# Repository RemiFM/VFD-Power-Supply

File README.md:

# VFD Power Supply

Power supply for the GP1294AI & GP1278BI (also marketed as VFD25648) vacuum fluorescent display. The supply requires a 12V input source, and outputs the necessary voltages to drive the anodes and filaments of the display. 

> [!CAUTION]
> The power supply outputs **voltages up to 75V** DC which can be hazardous. Handle with care.

## Usage
The VFD Display can be soldered to the front of the PCB. All components of the power supply are surface-mount technology (SMT) and are placed on the backside of the PCB. Only connect the display to the PCB after verifying all voltages on the power supply using the provided measuring points. The display can be controlled using any microcontroller that uses 3V3 logic (ESP32, Raspberry Pi...) using the general purpose 2.54mm male headers on the board.

## Ordering PCB
The production files necessary for manufacturing are bundled in the compressed folders [export/GP1294AI.zip](export/GP1294AI.zip) or [export/GP1278BI.zip](export/GP1278BI.zip), depending on the specific VFD display used. The gerber files are generated according to the guidelines of fabrication house JLCPCB. It is recommended to order the PCB from JLCPCB by uploading the compressed folder to their website, but other manufacturers (PCBWay, Eurocircuits...) should work as well.

## Ordering Components
A bill of materials (BOM) is available for download. The BOM contains Digi-Key part numbers, and is formatted in a way that can be uploaded to the Digi-Key website for effortless ordering.
Alternatively, the URL below leads to a public product list on Digi-Key which can be used for ordering the parts. As of June 2024, the total component cost is ~€23.

> [!TIP]
> Order all necessary components by following [this link](https://www.digikey.be/nl/mylists/list/VK1I6PIG8G). 

## Assembly
For assembly, please make use of the provided [schematic](schematic.pdf), available in pdf format.

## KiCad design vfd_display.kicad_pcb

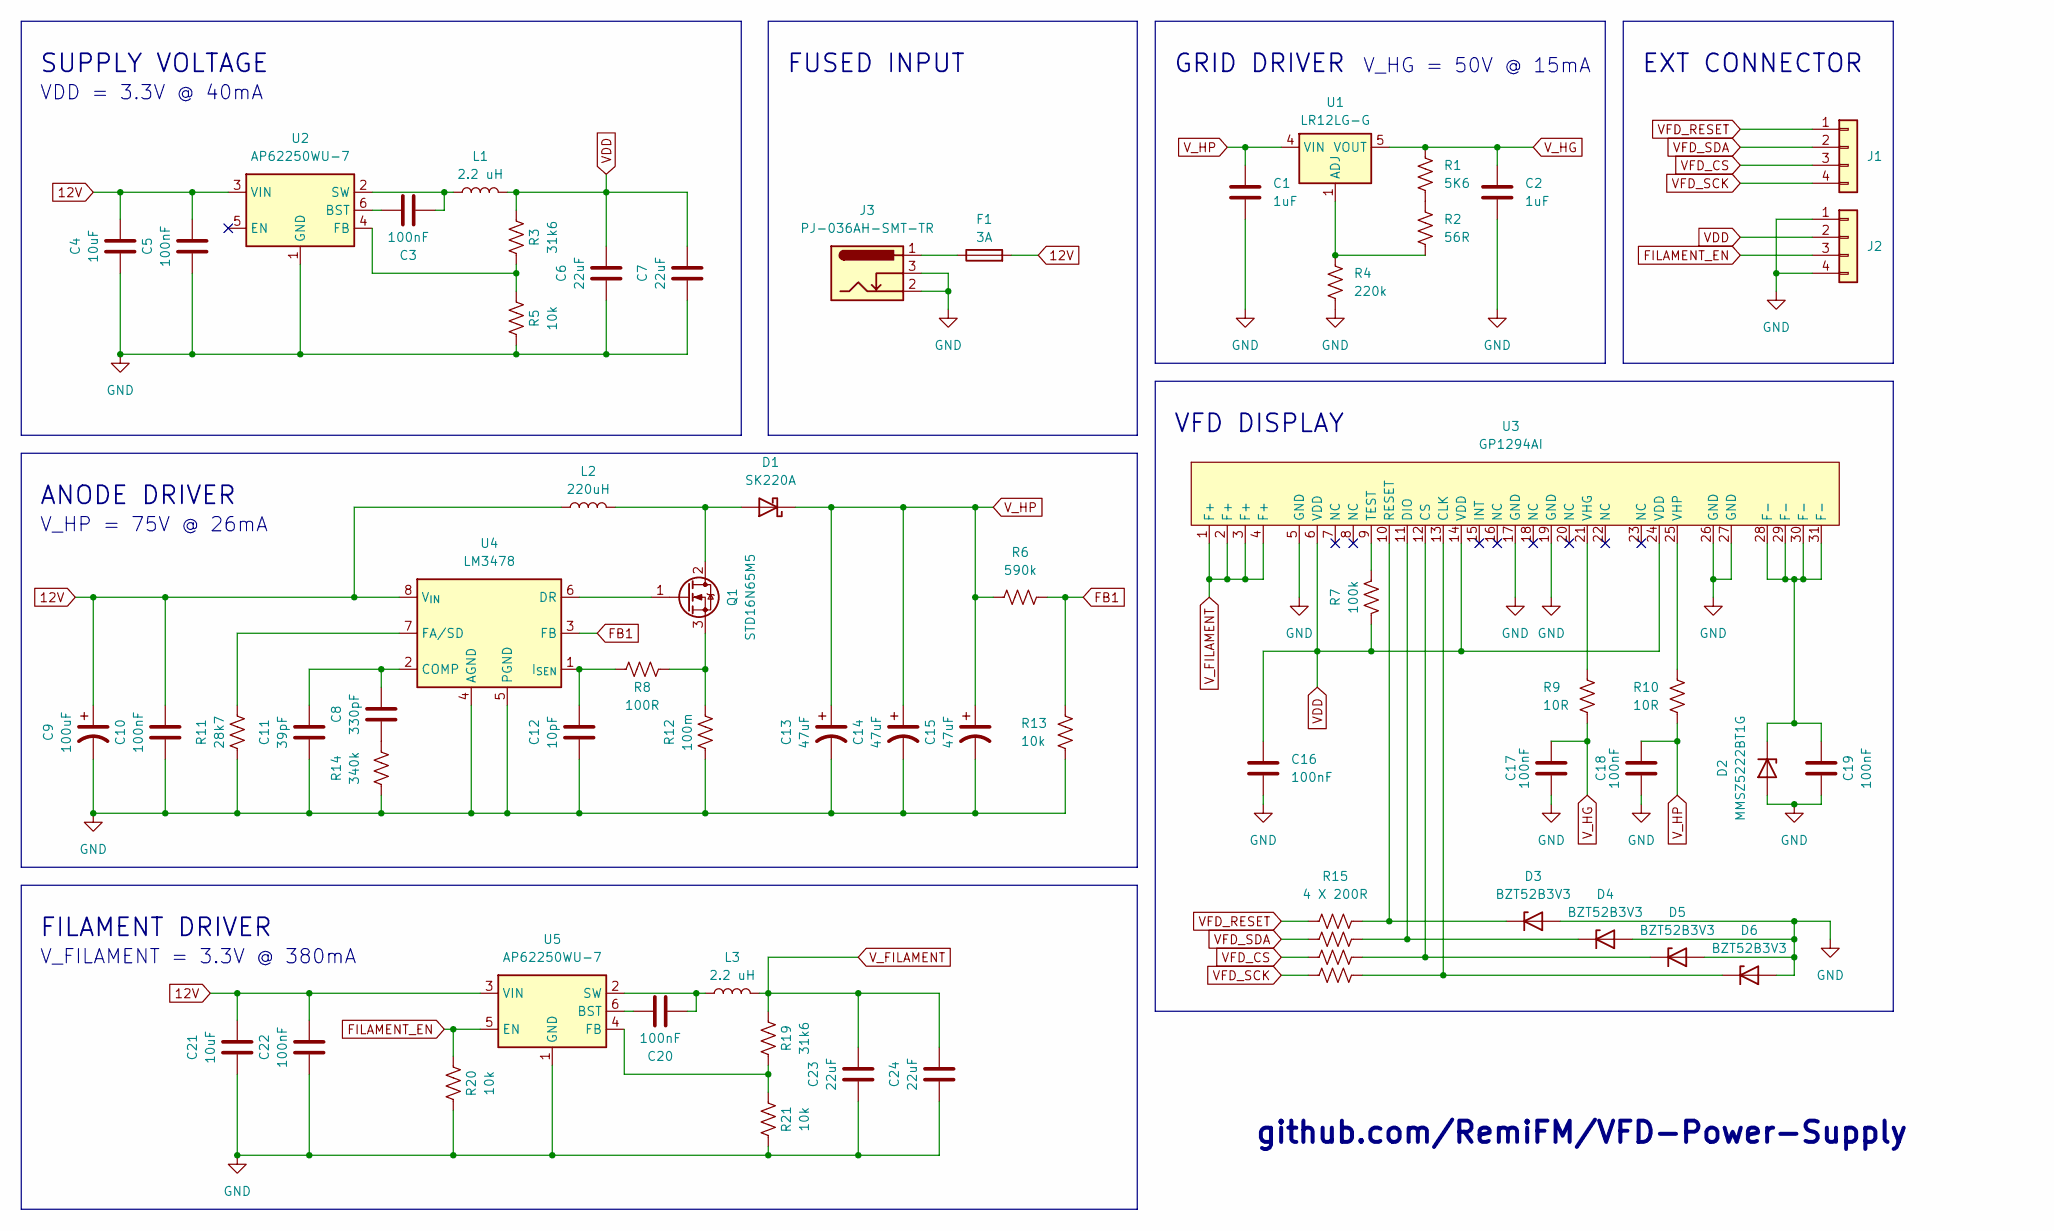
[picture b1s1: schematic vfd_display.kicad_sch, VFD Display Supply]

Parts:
C1, C2: 1uF; C_0805_2012Metric_Pad1.18x1.45mm_HandSolder
C3, C5, C10, C16, C17, C18, C19, C20, C22: 100nF; C_0805_2012Metric_Pad1.18x1.45mm_HandSolder
C4, C21: 10uF; C_0805_2012Metric_Pad1.18x1.45mm_HandSolder
C6, C7, C23, C24: 22uF; C_0805_2012Metric_Pad1.18x1.45mm_HandSolder
C8: 330pF; C_0805_2012Metric_Pad1.18x1.45mm_HandSolder
C9: 100uF; CP_Elec_6.3x7.7; Digi-Key 732-8254-1-ND
C11: 39pF; C_0805_2012Metric_Pad1.18x1.45mm_HandSolder
C12: 10pF; C_0805_2012Metric_Pad1.18x1.45mm_HandSolder
C13, C14, C15: 47uF; CP_Elec_10x10.5; Digi-Key 732-865060857005CT-ND
D1: SK220A; D_SMA_Handsoldering; Digi-Key 1655-SK220ACT-ND
D2: MMSZ5222BT1G; D_SOD-123; Digi-Key MMSZ5222BT1GOSCT-ND
D3, D4, D5, D6: BZT52B3V3; D_SOD-123F
F1: 3A; Fuse_0805_2012Metric_Pad1.15x1.40mm_HandSolder; DigiKeu MFU0805FF03000P100
J1: Conn_01x04; M20-8900405; Digi-Key 952-3265-ND
J2: Conn_01x04; M20-8900405; Digi-Key M20-8900405
J3: PJ-036AH-SMT-TR; BarrelJack_CUI_PJ-036AH-SMT_Horizontal
L1, L3: 2.2 uH; L_1008_2520Metric_Pad1.43x2.20mm_HandSolder; DigiKey 732-9690-1-ND
L2: 220uH; L_Wuerth_WE-PD-Typ-LS_Handsoldering; DigiKey 732-1696-1-ND
Q1: STD16N65M5; Digi-Key 497-8774-1-ND
R1: 5K6; R_0805_2012Metric_Pad1.20x1.40mm_HandSolder
R2: 56R; R_0805_2012Metric_Pad1.20x1.40mm_HandSolder
R3, R19: 31k6; R_0805_2012Metric_Pad1.20x1.40mm_HandSolder
R4: 220k; R_0805_2012Metric_Pad1.20x1.40mm_HandSolder
R5, R13, R20, R21: 10k; R_0805_2012Metric_Pad1.20x1.40mm_HandSolder
R6: 590k; R_0805_2012Metric_Pad1.20x1.40mm_HandSolder
R7: 100k; R_0805_2012Metric_Pad1.20x1.40mm_HandSolder
R8: 100R; R_0805_2012Metric_Pad1.20x1.40mm_HandSolder
R9, R10: 10R; R_0805_2012Metric_Pad1.20x1.40mm_HandSolder
R11: 28k7; R_0805_2012Metric_Pad1.20x1.40mm_HandSolder
R12: 100m; R_0805_2012Metric_Pad1.20x1.40mm_HandSolder
R14: 340k; R_0805_2012Metric_Pad1.20x1.40mm_HandSolder
R15: 4 X 200R; R_0805_2012Metric_Pad1.20x1.40mm_HandSolder
R16, R17, R18: 200R; R_0805_2012Metric_Pad1.20x1.40mm_HandSolder
U1: LR12LG-G; SOIC-8_3.9x4.9mm_P1.27mm; Digi-Key LR12LG-GCT-ND
U2, U5: AP62250WU-7; TSOT26
U3: GP1294AI; VFD_GP1294AI
U4: LM3478; SOIC-8_3.9x4.9mm_P1.27mm; Digi-Key 296-38111-1-ND

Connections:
12V: C4.1, C5.1, C9.1, C10.1, C21.1, C22.1, F1.2, L2.1, U2.3 (VIN), U4.8 (V_{IN}), U5.3 (VIN); also elsewhere on the board
FB1: R6.2, R13.1, U4.3 (FB)
FILAMENT_EN: J2.3, R20.2, U5.5 (EN)
GND: C1.2, C2.2, C4.2, C5.2, C6.2, C7.2, C9.2, C10.2, C11.2, C12.2, C13.2, C14.2, C15.2, C16.1, C17.2, C18.2, C19.2, C21.2, C22.2, C23.2, C24.2, D2.2 (A), D3.2 (A), D4.2 (A), D5.2 (A), D6.2 (A), J2.1, J2.4, J3.2, J3.3, R4.2, R5.1, R11.2, R12.2, R13.2, R14.2, R20.1, R21.1, U2.1 (GND), U3.5 (GND), U3.17 (GND), U3.19 (GND), U3.26 (GND), U3.27 (GND), U4.4 (AGND), U4.5 (PGND), U5.1 (GND); also elsewhere on the board
unnamed: C8.2, R14.1
unnamed: D1.2 (A), L2.2, Q1.2 (D)
unnamed: C19.1, D2.1 (K), U3.28 (F-), U3.29 (F-), U3.30 (F-), U3.31 (F-)
unnamed: D3.1 (K), R15.2, U3.10 (RESET)
unnamed: D4.1 (K), R16.2, U3.11 (DIO)
unnamed: D5.1 (K), R17.2, U3.12 (CS)
unnamed: D6.1 (K), R18.2, U3.13 (CLK)
unnamed: F1.1, J3.1
unnamed: Q1.1 (G), U4.6 (DR)
unnamed: Q1.3 (S), R8.2, R12.1
unnamed: R1.2, R2.1
unnamed: R2.2, R4.1, U1.1 (ADJ)
unnamed: C3.1, U2.6 (BST)
unnamed: R3.1, R5.2, U2.4 (FB)
unnamed: C3.2, L1.1, U2.2 (SW)
unnamed: R7.2, U3.9 (TEST)
unnamed: R9.1, U3.21 (VHG)
unnamed: R10.1, U3.25 (VHP)
unnamed: C8.1, C11.1, U4.2 (COMP)
unnamed: R11.1, U4.7 (FA/SD)
unnamed: C12.1, R8.1, U4.1 (I_{SEN})
unnamed: C20.1, U5.6 (BST)
unnamed: R19.1, R21.2, U5.4 (FB)
unnamed: C20.2, L3.1, U5.2 (SW)
VDD: C6.1, C7.1, C16.2, J2.2, L1.2, R3.2, R7.1, U3.6 (VDD), U3.14 (VDD), U3.24 (VDD); also elsewhere on the board
VFD_CS: J1.3, R17.1
VFD_RESET: J1.1, R15.1
VFD_SCK: J1.4, R18.1
VFD_SDA: J1.2, R16.1
V_FILAMENT: C23.1, C24.1, L3.2, R19.2, U3.1 (F+), U3.2 (F+), U3.3 (F+), U3.4 (F+); also elsewhere on the board
V_HG: C2.1, C17.1, R1.1, R9.2, U1.5 (VOUT); also elsewhere on the board
V_HP: C1.1, C13.1, C14.1, C15.1, C18.1, D1.1 (K), R6.1, R10.2, U1.4 (VIN); also elsewhere on the board

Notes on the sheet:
V_FILAMENT = 3.3V @ 380mA
SUPPLY VOLTAGE
VDD = 3.3V @ 40mA
FUSED INPUT
EXT CONNECTOR
V_HP = 75V @ 26mA
GRID DRIVER
FILAMENT DRIVER
github.com/RemiFM/VFD-Power-Supply
VFD DISPLAY
ANODE DRIVER
V_HG = 50V @ 15mA

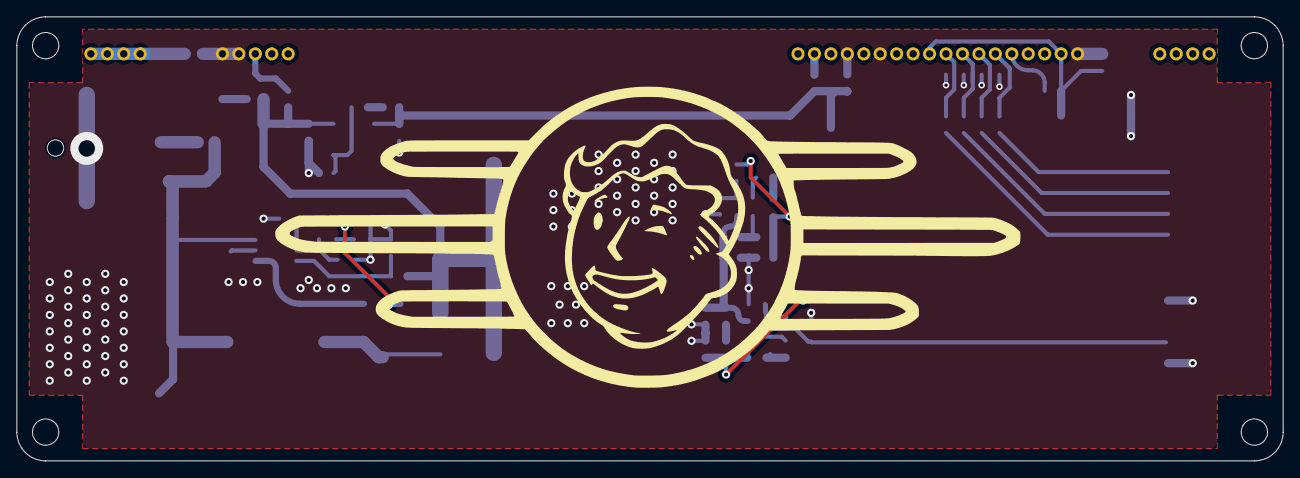
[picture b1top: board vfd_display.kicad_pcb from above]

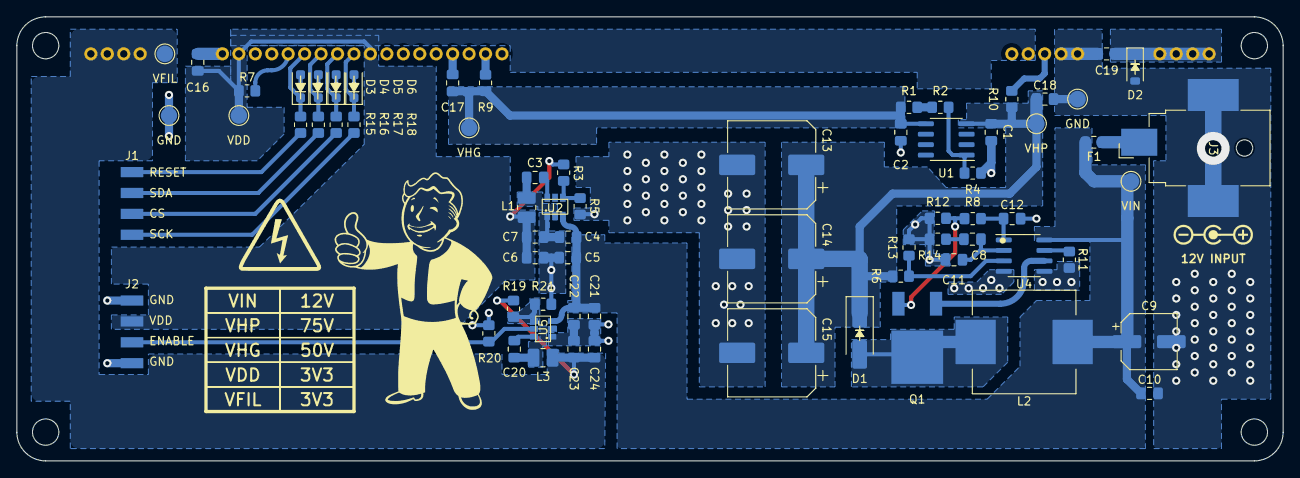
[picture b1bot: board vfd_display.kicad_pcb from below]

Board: 2 copper layers, 154.0 x 54.0 mm, 71 parts (70 on the bottom side), 36 nets.

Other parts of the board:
GND: TestPoint_Pad_D2.0mm
GND#2: TestPoint_Pad_D2.0mm
VDD: TestPoint_Pad_D2.0mm
VFIL: TestPoint_Pad_D2.0mm
VHG: TestPoint_Pad_D2.0mm
VHP: TestPoint_Pad_D2.0mm
VIN: TestPoint_Pad_D2.0mm

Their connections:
12V: VIN.1; also elsewhere on the board
GND: GND.1, GND#2.1; also elsewhere on the board
VDD: VDD.1; also elsewhere on the board
V_FILAMENT: VFIL.1; also elsewhere on the board
V_HG: VHG.1; also elsewhere on the board
V_HP: VHP.1; also elsewhere on the board

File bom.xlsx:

Group | Item | Designator | DigiKey | Cost | Number | Total | Remarks
Supply Voltage | Capacitor 10uF | C4 | 1276-1096-1-ND | 0.09 | 1 | 0.09 | footprint 0805
 | Capacitor 100nF | C5, C3 | 1276-6840-1-ND | 0.09 | 2 | 0.18 | footprint 0805
 | Capacitor 22uF | C6, C7 | 1276-6526-1-ND | 0.3 | 2 | 0.6 | footprint 0805
 | Resistor 31k6 | R3 | 311-31.6KCRCT-ND | 0.09 | 1 | 0.09 | footprint 0805
 | Resistor 10k | R5 | 311-10.0KCRCT-ND | 0.09 | 1 | 0.09 | footprint 0805
 | Inductor 2.2uH | L1 | 732-9690-1-ND | 0.49 | 1 | 0.49 | footprint 1008
 | Regulator AP62250 | U2 | 31-AP62250WU-7CT-ND | 0.3 | 1 | 0.3 | TSOT-26
Filament Driver | Capacitor 10uF | C21 | 1276-1096-1-ND | 0.09 | 1 | 0.09 | footprint 0805
 | Capacitor 100nF | C22, C20 | 1276-6840-1-ND | 0.09 | 2 | 0.18 | footprint 0805
 | Capacitor 22uF | C23, C24 | 1276-6526-1-ND | 0.3 | 2 | 0.6 | footprint 0805
 | Resistor 31k6 | R19 | 311-31.6KCRCT-ND | 0.09 | 1 | 0.09 | footprint 0805
 | Resistor 10k | R21, R20 | 311-10.0KCRCT-ND | 0.09 | 2 | 0.18 | footprint 0805
 | Inductor 2.2uH | L3 | 732-9690-1-ND | 0.49 | 1 | 0.49 | footprint 1008
 | Regulator AP62250 | U5 | 31-AP62250WU-7CT-ND | 0.3 | 1 | 0.3 | TSOT-26
Fused Input | Barrel Jack | J3 | CP-036AHPJCT-ND | 1.1399999999999999 | 1 | 1.1399999999999999
 | Barrel Plug | X | CP3-1000-ND | 1.1299999999999999 | 1 | 1.1299999999999999
 | 3A Fuse | F1 | MFU08053.00CT-ND | 0.56000000000000005 | 1 | 0.56000000000000005 | footprint 0805
Anode Driver | E-Capacitor 100uF | C9 | 732-8254-1-ND | 0.3 | 1 | 0.3
 | Capacitor 100nF | C10 | 1276-6840-1-ND | 0.09 | 1 | 0.09 | footprint 0805
 | Resistor 28k7 | R11 | 311-28.7KCRCT-ND | 0.09 | 1 | 0.09 | footprint 0805
 | Capacitor 39pF | C11 | 13-CC0805JRNPOBBN390CT-ND | 0.11 | 1 | 0.11 | HV, footprint 0805
 | Capacitor 330pF | C8 | 311-3287-1-ND | 0.13 | 1 | 0.13 | HV, footprint 0805
 | Capacitor 10pF | C12 | 311-4254-1-ND | 0.18 | 1 | 0.18 | HV, footprint 0805
 | Resistor 340k | R14 | 311-340KCRCT-ND | 0.09 | 1 | 0.09 | footprint 0805
 | Resistor 100R | R8 | 311-100CRCT-ND | 0.09 | 1 | 0.09 | footprint 0805
 | Resistor 0.1R | R12 | 311-0.1LUCT-ND | 0.39 | 1 | 0.39 | footprint 0805
 | Resistor 590k | R6 | 311-590KCRCT-ND | 0.09 | 1 | 0.09 | footprint 0805
 | Resistor 10k | R13 | 311-10.0KCRCT-ND | 0.09 | 1 | 0.09 | footprint 0805
 | Regulator LM3478 | U4 | 296-38111-1-ND | 2.41 | 1 | 2.41
 | Inductor 220uH | L2 | 732-1696-1-ND | 2.36 | 1 | 2.36
 | Diode SK220A | D1 | 1655-SK220ACT-ND | 0.41 | 1 | 0.41
 | Mosfet NCH | Q1 | 497-8774-1-ND | 2.69 | 1 | 2.69
 | E-Capacitor 47uF | C13, C14, C15 | 399-14797-1-ND | 0.68 | 3 | 2.04 | HV
Grid Driver | Capacitor 1uF | C1, C2 | 1276-1066-1-ND | 0.09 | 2 | 0.18 | footprint 0805
 | Resistor 220k | R4 | 311-220KARCT-ND | 0.09 | 1 | 0.09 | footprint 0806
 | Resistor 5K6 | R1 | 311-5.6KARCT-ND | 0.09 | 1 | 0.09 | footprint 0807
 | Resistor 56R | R2 | 311-56ARCT-ND | 0.09 | 1 | 0.09 | footprint 0808
 | Regulator | U1 | LR12LG-GCT-ND | 1.54 | 1 | 1.54
Connector | Male connector | J1, J2 | 952-3265-ND | 0.61 | 2 | 1.22
VFD Display | Resistor 200R | R15, R16, R17, R18 | 311-200CRCT-ND | 0.09 | 4 | 0.36
 | Resistor 100k | R7 | 311-100KCRCT-ND | 0.09 | 1 | 0.09
 | Resistor 10R | R9, R10 | 13-AC0805FR-7W10RLCT-ND | 0.09 | 2 | 0.18 | HV
 | Capacitor 100nF | C16, C19, C17, C18 | 1276-6840-1-ND | 0.09 | 4 | 0.36
 | Diode BZT52B3V3 | D3, D4, D5, D6 | BZT52B3V3RHGCT-ND | 0.19 | 4 | 0.76
 | Zener Diode | D2 | MMSZ5222BT1GOSCT-ND | 0.21 | 1 | 0.21
 |  |  |  |  |  | 23.329999999999995

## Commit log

2024-06-10 BOM Update
2024-06-10 gitignore
2024-06-10 3D Component Models
2024-06-10 Image upload
2024-06-10 BOM Updates
2024-06-10 Fabrication outputs
2024-06-12 Add teardrops
2024-06-14 Minor tweaks
2024-06-14 GP1278BI Variation
